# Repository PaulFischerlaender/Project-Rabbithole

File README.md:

# Project Rabbithole

Keep in mind that this project is still WORK IN PROGRESS!

A 60% ANSI layout alice style keyboard with a switch integrated rotary encoder support.

The case is made out of stacked acrylic and M.2 screws.

TODO: 
      
      -Adding an ISO version, 'cause we all love ISO layout :)
      
      -Adding a non Elite-C version of the PCB
      
      -Possibly adding a l2c OLED display support

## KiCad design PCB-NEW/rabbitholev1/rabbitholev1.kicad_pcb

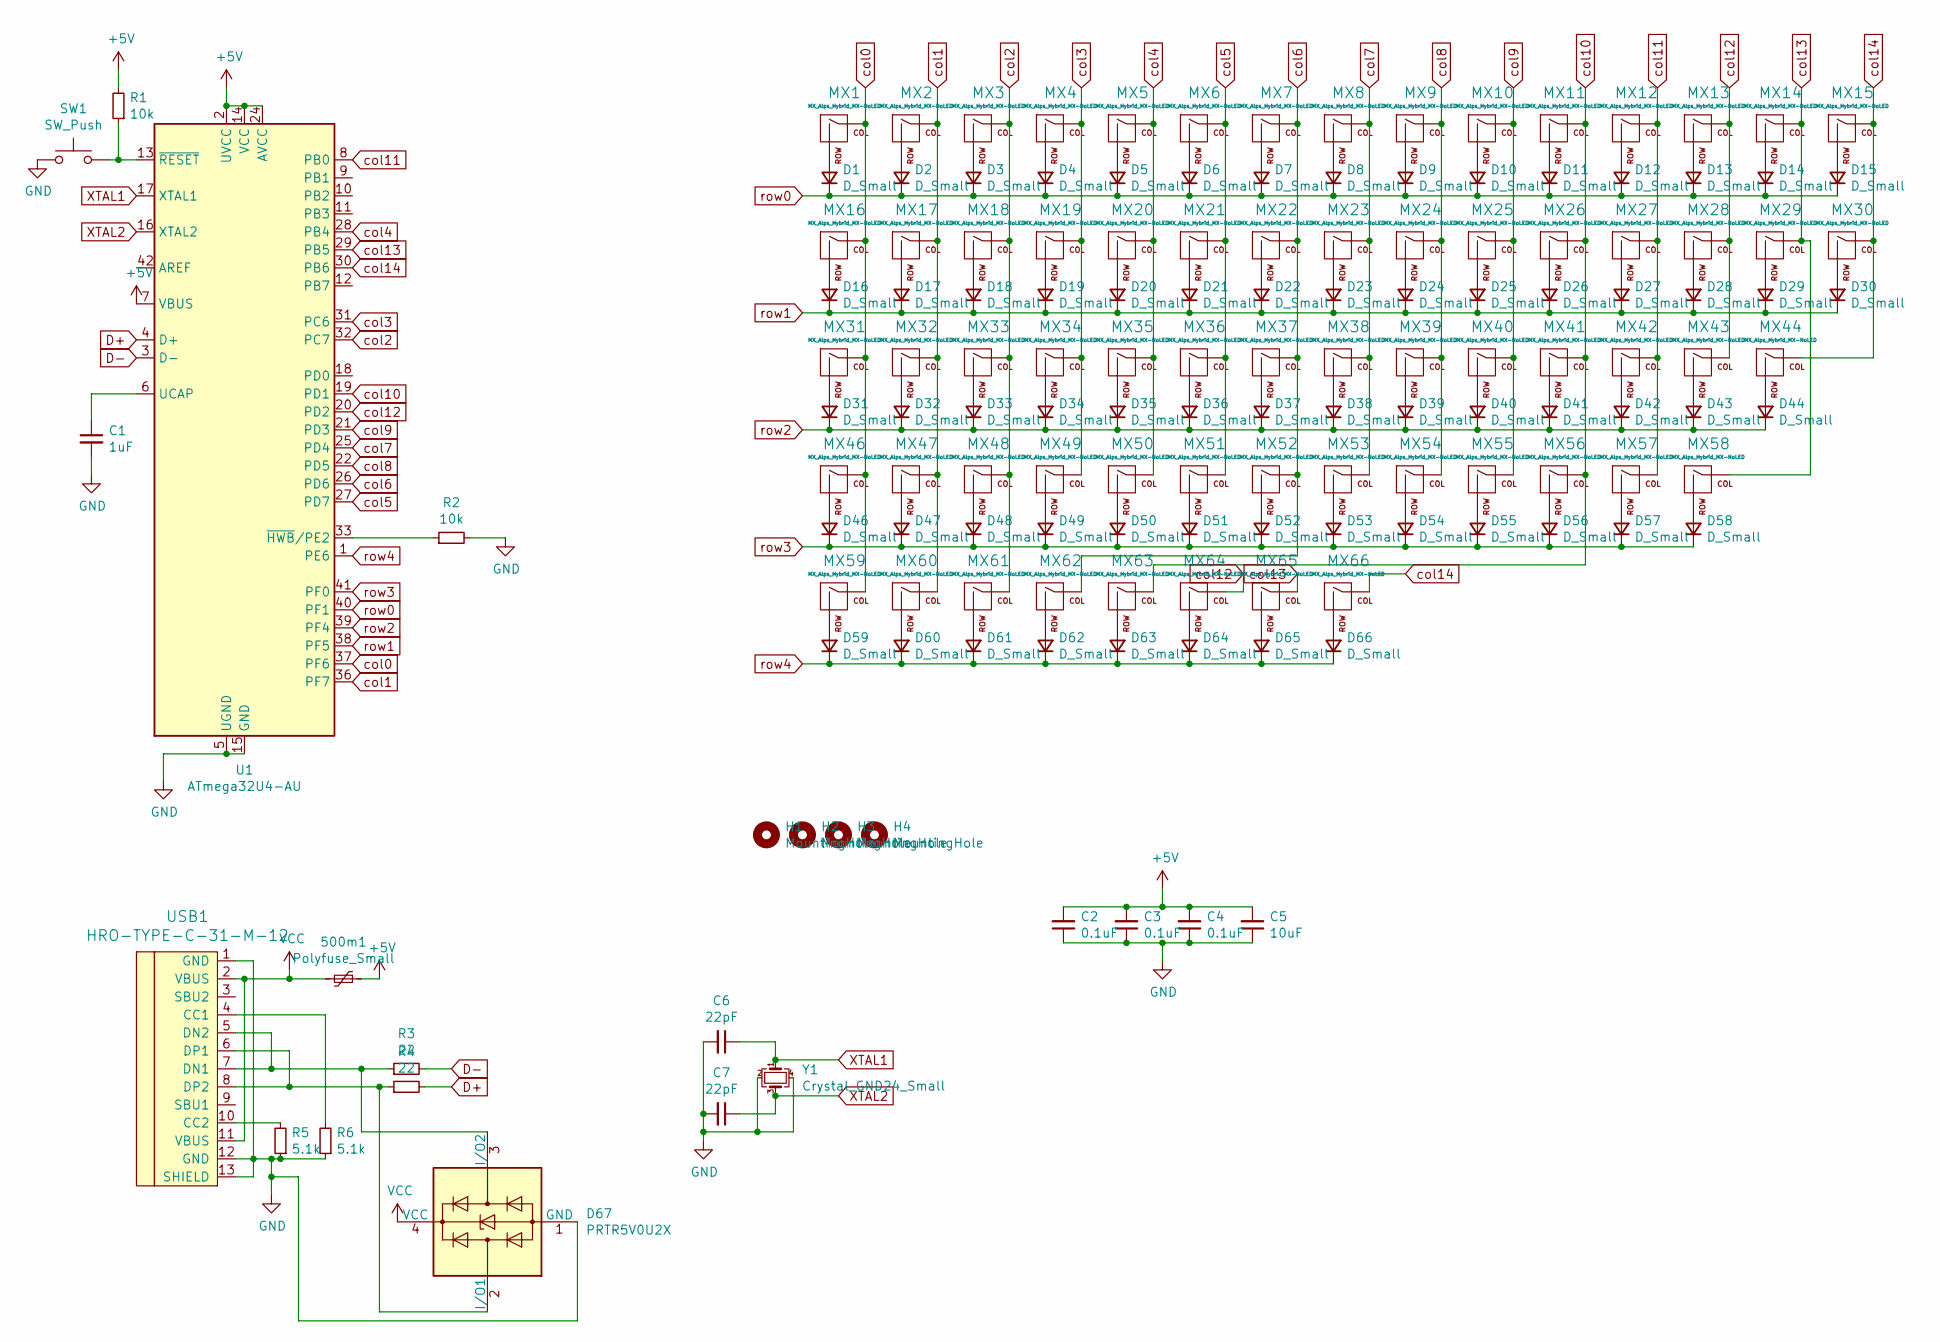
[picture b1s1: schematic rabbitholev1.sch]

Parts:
500m1: Polyfuse_Small; Fuse_1206_3216Metric
C1: 1uF; C_0805_2012Metric
C2, C3, C4: 0.1uF; C_0805_2012Metric
C5: 10uF; C_0805_2012Metric
C6, C7: 22pF; C_0805_2012Metric
D1, D2, D3, D4, D5, D6, D7, D8, D9, D10, D11, D12, D13, D14, D15, D16, D17, D18, D19, D20, D21, D22, D23, D24, D25, D26, D27, D28, D29, D30, D31, D32, D33, D34, D35, D36, D37, D38, D39, D40, D41, D42, D43, D44, D46, D47, D48, D49, D50, D51, D52, D53, D54, D55, D56, D57, D58, D59, D60, D61, D62, D63, D64, D65, D66: D_Small; D_SOD-123
D67: PRTR5V0U2X; SOT-143
H1, H2, H3, H4: MountingHole
MX1, MX2, MX3, MX4, MX5, MX6, MX7, MX8, MX9, MX10, MX11, MX12, MX13, MX15, MX17, MX18, MX19, MX20, MX21, MX22, MX23, MX24, MX25, MX26, MX27, MX28, MX30, MX32, MX33, MX34, MX35, MX36, MX37, MX38, MX39, MX40, MX41, MX42, MX43, MX44, MX47, MX48, MX49, MX50, MX51, MX52, MX53, MX54, MX55, MX56, MX57, MX58, MX64, MX65, MX66: MX_Alps_Hybrid_MX-NoLED; MXOnly-1U-NoLED
MX14: MX_Alps_Hybrid_MX-NoLED; MXOnly-2U-NoLED
MX16: MX_Alps_Hybrid_MX-NoLED; MXOnly-1.5U-NoLED
MX29: MX_Alps_Hybrid_MX-NoLED; MXOnly-ISO
MX31: MX_Alps_Hybrid_MX-NoLED; MXOnly-1.75U-NoLED
MX46, MX59, MX60, MX61, MX63: MX_Alps_Hybrid_MX-NoLED; MXOnly-1.25U-NoLED
MX62: MX_Alps_Hybrid_MX-NoLED; MXOnly-6.25U-NoLED
R1, R2: 10k; R_0805_2012Metric
R3, R4: 22; R_0805_2012Metric
R5, R6: 5.1k; R_0805_2012Metric
SW1: SW_Push; SKQG-1155865
U1: ATmega32U4-AU; TQFP-44_10x10mm_P0.8mm
USB1: HRO-TYPE-C-31-M-12
Y1: Crystal_GND24_Small; Crystal_SMD_3225-4Pin_3.2x2.5mm

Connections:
+5V: 500m1.1, C2.2, C3.2, C4.2, C5.2, R1.2, U1.2 (UVCC), U1.7 (VBUS), U1.14 (VCC), U1.24 (AVCC), U1.34 (VCC), U1.44 (AVCC)
D+: R4.2, U1.4 (D+)
D-: R3.2, U1.3 (D-)
GND: C1.2, C2.1, C3.1, C4.1, C5.1, C6.2, C7.2, D67.1 (GND), R2.2, R5.1, R6.1, SW1.1, U1.5 (UGND), U1.15 (GND), U1.23 (GND), U1.35 (GND), U1.43 (GND), USB1.1 (GND), USB1.12 (GND), USB1.13 (SHIELD), Y1.2, Y1.4
unnamed: C1.1, U1.6 (UCAP)
unnamed: D1.2 (A), MX1.2 (ROW)
unnamed: D2.2 (A), MX2.2 (ROW)
unnamed: D3.2 (A), MX3.2 (ROW)
unnamed: D4.2 (A), MX4.2 (ROW)
unnamed: D5.2 (A), MX5.2 (ROW)
unnamed: D6.2 (A), MX6.2 (ROW)
unnamed: D7.2 (A), MX7.2 (ROW)
unnamed: D8.2 (A), MX8.2 (ROW)
unnamed: D9.2 (A), MX9.2 (ROW)
unnamed: D10.2 (A), MX10.2 (ROW)
unnamed: D11.2 (A), MX11.2 (ROW)
unnamed: D12.2 (A), MX12.2 (ROW)
unnamed: D13.2 (A), MX13.2 (ROW)
unnamed: D14.2 (A), MX14.2 (ROW)
unnamed: D15.2 (A), MX15.2 (ROW)
unnamed: D16.2 (A), MX16.2 (ROW)
unnamed: D17.2 (A), MX17.2 (ROW)
unnamed: D18.2 (A), MX18.2 (ROW)
unnamed: D19.2 (A), MX19.2 (ROW)
unnamed: D20.2 (A), MX20.2 (ROW)
unnamed: D21.2 (A), MX21.2 (ROW)
unnamed: D22.2 (A), MX22.2 (ROW)
unnamed: D23.2 (A), MX23.2 (ROW)
unnamed: D24.2 (A), MX24.2 (ROW)
unnamed: D25.2 (A), MX25.2 (ROW)
unnamed: D26.2 (A), MX26.2 (ROW)
unnamed: D27.2 (A), MX27.2 (ROW)
unnamed: D28.2 (A), MX28.2 (ROW)
unnamed: D29.2 (A), MX29.2 (ROW)
unnamed: D30.2 (A), MX30.2 (ROW)
unnamed: D31.2 (A), MX31.2 (ROW)
unnamed: D32.2 (A), MX32.2 (ROW)
unnamed: D33.2 (A), MX33.2 (ROW)
unnamed: D34.2 (A), MX34.2 (ROW)
unnamed: D35.2 (A), MX35.2 (ROW)
unnamed: D36.2 (A), MX36.2 (ROW)
unnamed: D37.2 (A), MX37.2 (ROW)
unnamed: D38.2 (A), MX38.2 (ROW)
unnamed: D39.2 (A), MX39.2 (ROW)
unnamed: D40.2 (A), MX40.2 (ROW)
unnamed: D41.2 (A), MX41.2 (ROW)
unnamed: D42.2 (A), MX42.2 (ROW)
unnamed: D43.2 (A), MX43.2 (ROW)
unnamed: D44.2 (A), MX44.2 (ROW)
unnamed: D46.2 (A), MX46.2 (ROW)
unnamed: D47.2 (A), MX47.2 (ROW)
unnamed: D48.2 (A), MX48.2 (ROW)
unnamed: D49.2 (A), MX49.2 (ROW)
unnamed: D50.2 (A), MX50.2 (ROW)
unnamed: D51.2 (A), MX51.2 (ROW)
unnamed: D52.2 (A), MX52.2 (ROW)
unnamed: D53.2 (A), MX53.2 (ROW)
unnamed: D54.2 (A), MX54.2 (ROW)
unnamed: D55.2 (A), MX55.2 (ROW)
unnamed: D56.2 (A), MX56.2 (ROW)
unnamed: D57.2 (A), MX57.2 (ROW)
unnamed: D58.2 (A), MX58.2 (ROW)
unnamed: D59.2 (A), MX59.2 (ROW)
unnamed: D60.2 (A), MX60.2 (ROW)
unnamed: D61.2 (A), MX61.2 (ROW)
unnamed: D62.2 (A), MX62.2 (ROW)
unnamed: D63.2 (A), MX63.2 (ROW)
unnamed: D64.2 (A), MX64.2 (ROW)
unnamed: D65.2 (A), MX65.2 (ROW)
unnamed: D66.2 (A), MX66.2 (ROW)
unnamed: D67.2 (I/O1), R4.1, USB1.6 (DP1), USB1.8 (DP2)
unnamed: D67.3 (I/O2), R3.1, USB1.5 (DN2), USB1.7 (DN1)
unnamed: R1.1, SW1.2, U1.13 (~RESET)
unnamed: R2.1, U1.33 (~HWB~/PE2)
unnamed: R5.2, USB1.10 (CC2)
unnamed: R6.2, USB1.4 (CC1)
VCC: 500m1.2, D67.4 (VCC), USB1.2 (VBUS), USB1.11 (VBUS)
XTAL1: C6.1, U1.17 (XTAL1), Y1.1
XTAL2: C7.1, U1.16 (XTAL2), Y1.3
col0: MX1.1 (COL), MX16.1 (COL), MX31.1 (COL), MX46.1 (COL), MX59.1 (COL), U1.37 (PF6)
col1: MX2.1 (COL), MX17.1 (COL), MX32.1 (COL), MX47.1 (COL), MX60.1 (COL), U1.36 (PF7)
col2: MX3.1 (COL), MX18.1 (COL), MX33.1 (COL), MX48.1 (COL), MX61.1 (COL), U1.32 (PC7)
col3: MX4.1 (COL), MX19.1 (COL), MX34.1 (COL), MX49.1 (COL), U1.31 (PC6)
col4: MX5.1 (COL), MX20.1 (COL), MX35.1 (COL), MX50.1 (COL), U1.28 (PB4)
col5: MX6.1 (COL), MX21.1 (COL), MX36.1 (COL), MX51.1 (COL), U1.27 (PD7)
col6: MX7.1 (COL), MX22.1 (COL), MX37.1 (COL), MX52.1 (COL), MX62.1 (COL), U1.26 (PD6)
col7: MX8.1 (COL), MX23.1 (COL), MX38.1 (COL), MX53.1 (COL), U1.25 (PD4)
col8: MX9.1 (COL), MX24.1 (COL), MX39.1 (COL), MX54.1 (COL), U1.22 (PD5)
col9: MX10.1 (COL), MX25.1 (COL), MX40.1 (COL), MX55.1 (COL), U1.21 (PD3)
col10: MX11.1 (COL), MX26.1 (COL), MX41.1 (COL), MX56.1 (COL), MX63.1 (COL), U1.19 (PD1)
col11: MX12.1 (COL), MX27.1 (COL), MX42.1 (COL), MX57.1 (COL), U1.8 (PB0)
col12: MX13.1 (COL), MX28.1 (COL), MX43.1 (COL), MX64.1 (COL), U1.20 (PD2)
col13: MX14.1 (COL), MX29.1 (COL), MX58.1 (COL), MX65.1 (COL), U1.29 (PB5)
col14: MX15.1 (COL), MX30.1 (COL), MX44.1 (COL), MX66.1 (COL), U1.30 (PB6)
row0: D1.1 (K), D2.1 (K), D3.1 (K), D4.1 (K), D5.1 (K), D6.1 (K), D7.1 (K), D8.1 (K), D9.1 (K), D10.1 (K), D11.1 (K), D12.1 (K), D13.1 (K), D14.1 (K), D15.1 (K), U1.40 (PF1)
row1: D16.1 (K), D17.1 (K), D18.1 (K), D19.1 (K), D20.1 (K), D21.1 (K), D22.1 (K), D23.1 (K), D24.1 (K), D25.1 (K), D26.1 (K), D27.1 (K), D28.1 (K), D29.1 (K), D30.1 (K), U1.38 (PF5)
row2: D31.1 (K), D32.1 (K), D33.1 (K), D34.1 (K), D35.1 (K), D36.1 (K), D37.1 (K), D38.1 (K), D39.1 (K), D40.1 (K), D41.1 (K), D42.1 (K), D43.1 (K), D44.1 (K), U1.39 (PF4)
row3: D46.1 (K), D47.1 (K), D48.1 (K), D49.1 (K), D50.1 (K), D51.1 (K), D52.1 (K), D53.1 (K), D54.1 (K), D55.1 (K), D56.1 (K), D57.1 (K), D58.1 (K), U1.41 (PF0)
row4: D59.1 (K), D60.1 (K), D61.1 (K), D62.1 (K), D63.1 (K), D64.1 (K), D65.1 (K), D66.1 (K), U1.1 (PE6)

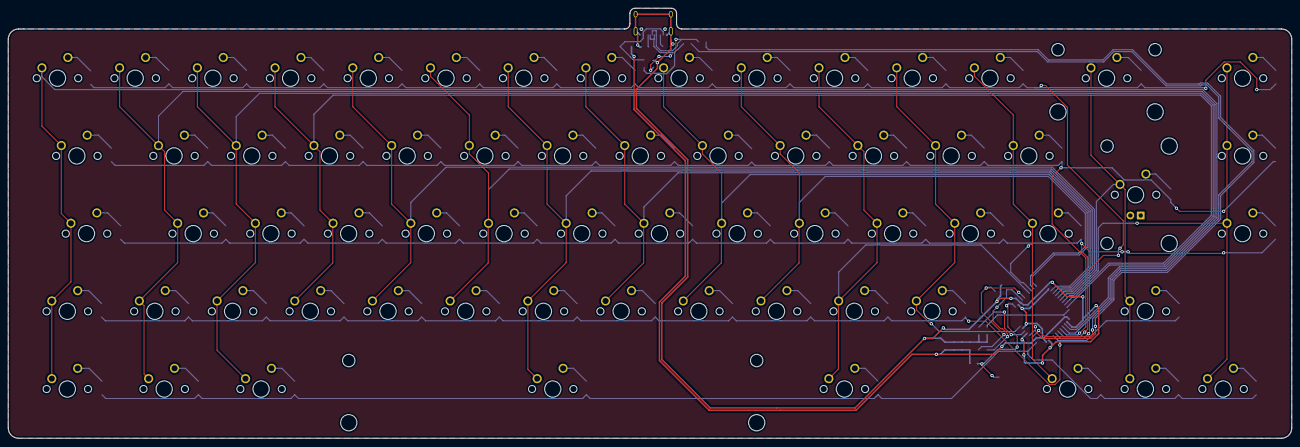
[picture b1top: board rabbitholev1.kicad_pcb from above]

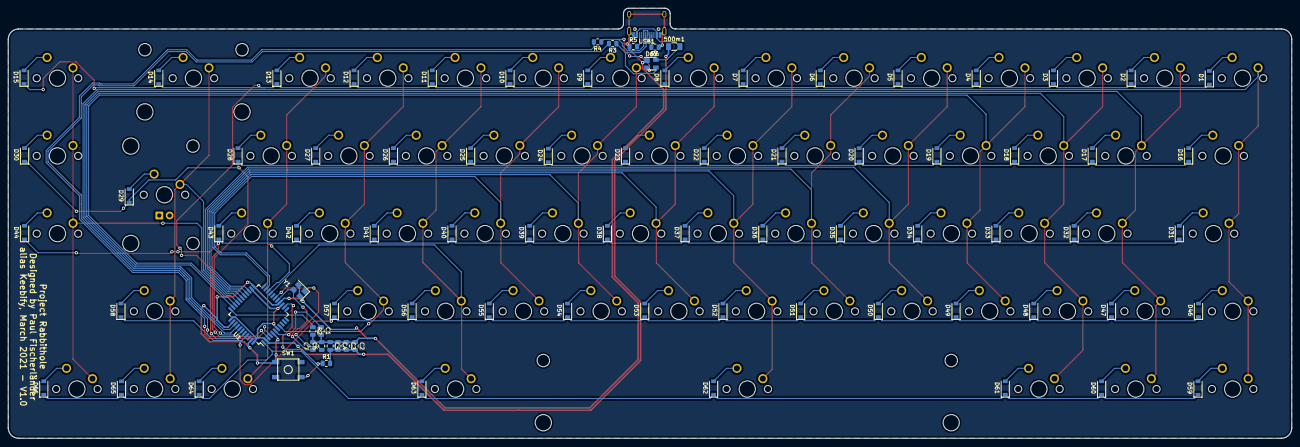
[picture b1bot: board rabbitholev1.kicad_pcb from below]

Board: 2 copper layers, 314.6 x 105.4 mm, 149 parts (84 on the bottom side), 99 nets.

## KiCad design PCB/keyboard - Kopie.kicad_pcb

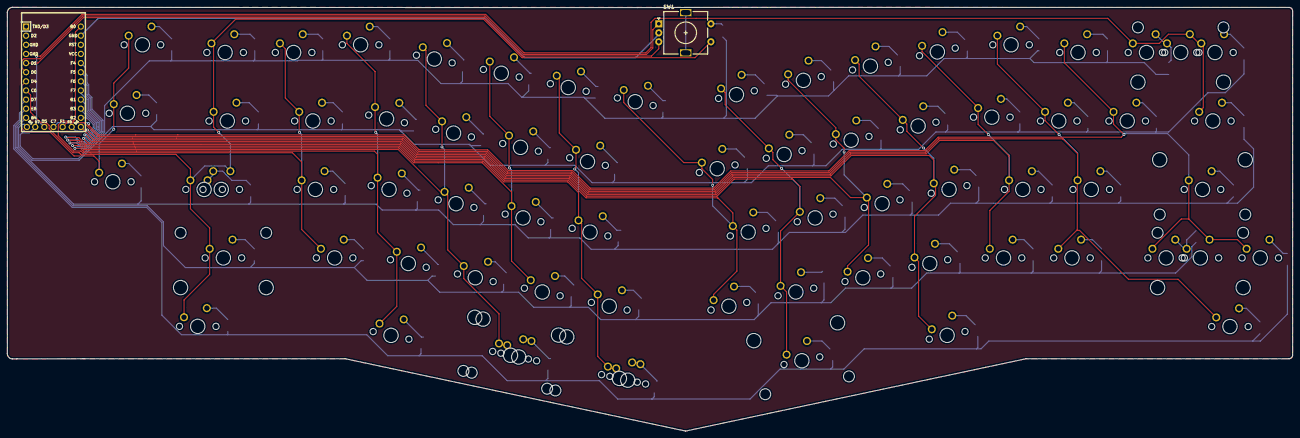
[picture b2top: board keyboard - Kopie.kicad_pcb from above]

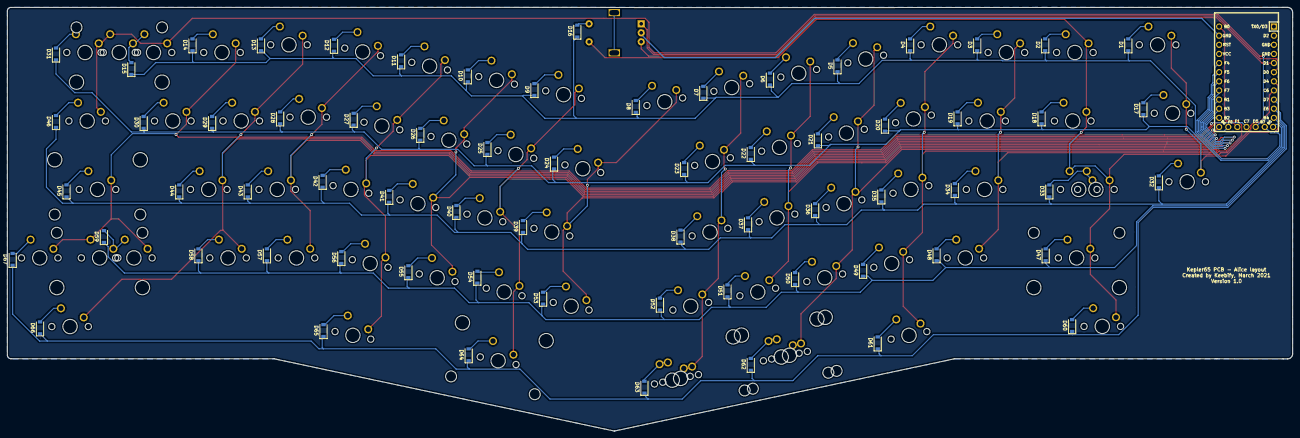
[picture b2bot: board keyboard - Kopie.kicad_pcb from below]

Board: 2 copper layers, 357.6 x 117.9 mm, 140 parts (67 on the bottom side), 90 nets.

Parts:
D1, D2, D3, D4, D5, D6, D7, D8, D9, D10, D11, D12, D13, D14, D15, D16, D17, D18, D19, D20, D21, D22, D23, D24, D25, D26, D27, D28, D29, D30, D31, D32, D33, D34, D35, D36, D37, D38, D39, D40, D41, D42, D43, D44, D45, D46, D47, D48, D49, D50, D51, D52, D53, D54, D55, D56, D57, D58, D59, D60, D61, D62, D63, D64, D65, D66, D67: D_Small; D_SOD-123
K_0, K_1, K_2, K_3, K_4, K_5, K_6, K_7, K_8, K_9, K_10, K_11, K_12, K_13, K_14, K_15, K_17, K_18, K_19, K_20, K_21, K_22, K_23, K_24, K_25, K_26, K_27, K_28, K_29, K_30, K_32, K_33, K_34, K_35, K_36, K_37, K_38, K_39, K_40, K_41, K_42, K_46, K_47, K_48, K_49, K_50, K_51, K_52, K_53, K_54, K_55, K_56, K_65: KEYSW; MXOnly-1U-NoLED
K_16, K_44, K_58, K_59, K_63, K_64: KEYSW; MXOnly-1.5U-NoLED
K_31, K_57: KEYSW; MXOnly-1.75U-NoLED
K_43: KEYSW; MXOnly-2.25U-ReversedStabilizers-NoLED
K_45: KEYSW; MXOnly-2.25U-NoLED
K_60: KEYSW; MXOnly-2U-ReversedStabilizers-NoLED
K_61: KEYSW; MXOnly-1.25U-NoLED
K_62: KEYSW; MXOnly-2.75U-ReversedStabilizers-NoLED
K_142: MX-NoLED; MXOnly-2U-NoLED
K_312, K_612: MX-NoLED; MXOnly-1U-NoLED
K_572: MX-NoLED; MXOnly-2.75U-NoLED
K_602: MX-NoLED; MXOnly-2.25U-ReversedStabilizers-NoLED
SW1: Rotary_Encoder_Switch; RotaryEncoder_Alps_EC11E-Switch_Vertical_H20mm
U1: Elite-C

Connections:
GND: SW1.C, U1.23
unnamed: D1.2, K_0.2
unnamed: D2.2, K_1.2
unnamed: D3.2, K_2.2
unnamed: D4.2, K_3.2
unnamed: D5.2, K_4.2
unnamed: D6.2, K_5.2
unnamed: D7.2, K_6.2
unnamed: D8.2, K_7.2
unnamed: D9.2, K_8.2
unnamed: D10.2, K_9.2
unnamed: D11.2, K_10.2
unnamed: D12.2, K_11.2
unnamed: D13.2, K_12.2
unnamed: D14.2, K_13.2
unnamed: D15.2, K_14.2, K_142.1
unnamed: D16.2, SW1.S2
unnamed: D17.2, K_15.2
unnamed: D18.2, K_16.2
unnamed: D19.2, K_17.2
unnamed: D20.2, K_18.2
unnamed: D21.2, K_19.2
unnamed: D22.2, K_20.2
unnamed: D23.2, K_21.2
unnamed: D24.2, K_22.2
unnamed: D25.2, K_23.2
unnamed: D26.2, K_24.2
unnamed: D27.2, K_25.2
unnamed: D28.2, K_26.2
unnamed: D29.2, K_27.2
unnamed: D30.2, K_28.2
unnamed: D31.2, K_29.2
unnamed: D32.2, K_30.2
unnamed: D33.2, K_31.2, K_312.1
unnamed: D34.2, K_32.2
unnamed: D35.2, K_33.2
unnamed: D36.2, K_34.2
unnamed: D37.2, K_35.2
unnamed: D38.2, K_36.2
unnamed: D39.2, K_37.2
unnamed: D40.2, K_38.2
unnamed: D41.2, K_39.2
unnamed: D42.2, K_40.2
unnamed: D43.2, K_41.2
unnamed: D44.2, K_42.2
unnamed: D45.2, K_43.2
unnamed: D46.2, K_44.2
unnamed: D47.2, K_45.2
unnamed: D48.2, K_46.2
unnamed: D49.2, K_47.2
unnamed: D50.2, K_48.2
unnamed: D51.2, K_49.2
unnamed: D52.2, K_50.2
unnamed: D53.2, K_51.2
unnamed: D54.2, K_52.2
unnamed: D55.2, K_53.2
unnamed: D56.2, K_54.2
unnamed: D57.2, K_55.2
unnamed: D58.2, K_56.2
unnamed: D59.2, K_57.2, K_572.1
unnamed: D60.2, K_58.2
unnamed: D61.2, K_59.2
unnamed: D62.2, K_60.2, K_602.2
unnamed: D63.2, K_61.2, K_612.2
unnamed: D64.2, K_62.2
unnamed: D65.2, K_63.2
unnamed: D66.2, K_64.2
unnamed: D67.2, K_65.2
ROT_A: SW1.A, U1.6
ROT_B: SW1.B, U1.5
col0: K_0.1, K_15.1, K_30.1, U1.7
col1: K_1.1, K_16.1, K_31.1, K_45.1, K_58.1, K_312.2, SW1.S1, U1.8
col2: K_2.1, K_17.1, K_32.1, K_46.1, U1.24
col3: K_3.1, K_18.1, K_33.1, K_47.1, K_59.1, U1.20
col4: K_4.1, K_19.1, K_34.1, K_48.1, K_60.1, K_602.1, U1.19
col5: K_5.1, K_20.1, K_35.1, K_49.1, U1.18
col6: K_6.1, K_21.1, K_36.1, K_50.1, K_61.1, K_612.1, U1.17
col7: K_7.1, K_22.1, K_37.1, K_51.1, U1.16
col8: K_8.1, K_23.1, K_38.1, K_52.1, K_62.1, U1.15
col9: K_9.1, K_24.1, K_39.1, K_53.1, U1.14
col10: K_10.1, K_25.1, K_40.1, K_54.1, K_63.1, U1.13
col11: K_11.1, K_26.1, K_41.1, K_55.1, U1.29
col12: K_12.1, K_27.1, K_42.1, K_56.1, K_64.1, U1.28
col13: K_13.1, K_28.1, K_43.1, K_57.1, K_65.1, K_572.2, U1.27
col14: K_14.1, K_29.1, K_44.1, K_142.2, U1.26
row0: D1.1, D2.1, D3.1, D4.1, D5.1, D6.1, D7.1, D8.1, D9.1, D10.1, D11.1, D12.1, D13.1, D14.1, D15.1, D16.1, U1.25
row1: D17.1, D18.1, D19.1, D20.1, D21.1, D22.1, D23.1, D24.1, D25.1, D26.1, D27.1, D28.1, D29.1, D30.1, D31.1, U1.12
row2: D32.1, D33.1, D34.1, D35.1, D36.1, D37.1, D38.1, D39.1, D40.1, D41.1, D42.1, D43.1, D44.1, D45.1, D46.1, U1.11
row3: D47.1, D48.1, D49.1, D50.1, D51.1, D52.1, D53.1, D54.1, D55.1, D56.1, D57.1, D58.1, D59.1, U1.10
row4: D60.1, D61.1, D62.1, D63.1, D64.1, D65.1, D66.1, D67.1, U1.9

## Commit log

2021-03-22 v.1.0
2021-03-24 V1.1
